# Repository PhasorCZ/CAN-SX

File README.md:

# CAN-SX
Modular automotive electronics system based on CAN bus for resto-mods.

### Description
xxx

### Motivation
xxx

### License
- SOFTWARE: GNU General Public License Version 3
- HARDWARE: CERN Open Hardware Licence Version 2 - Strongly Reciprocal

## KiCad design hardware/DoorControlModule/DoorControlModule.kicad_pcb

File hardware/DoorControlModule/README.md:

# Door Control Module
xxx

### Description
xxx

### License
CERN Open Hardware Licence Version 2 - Strongly Reciprocal

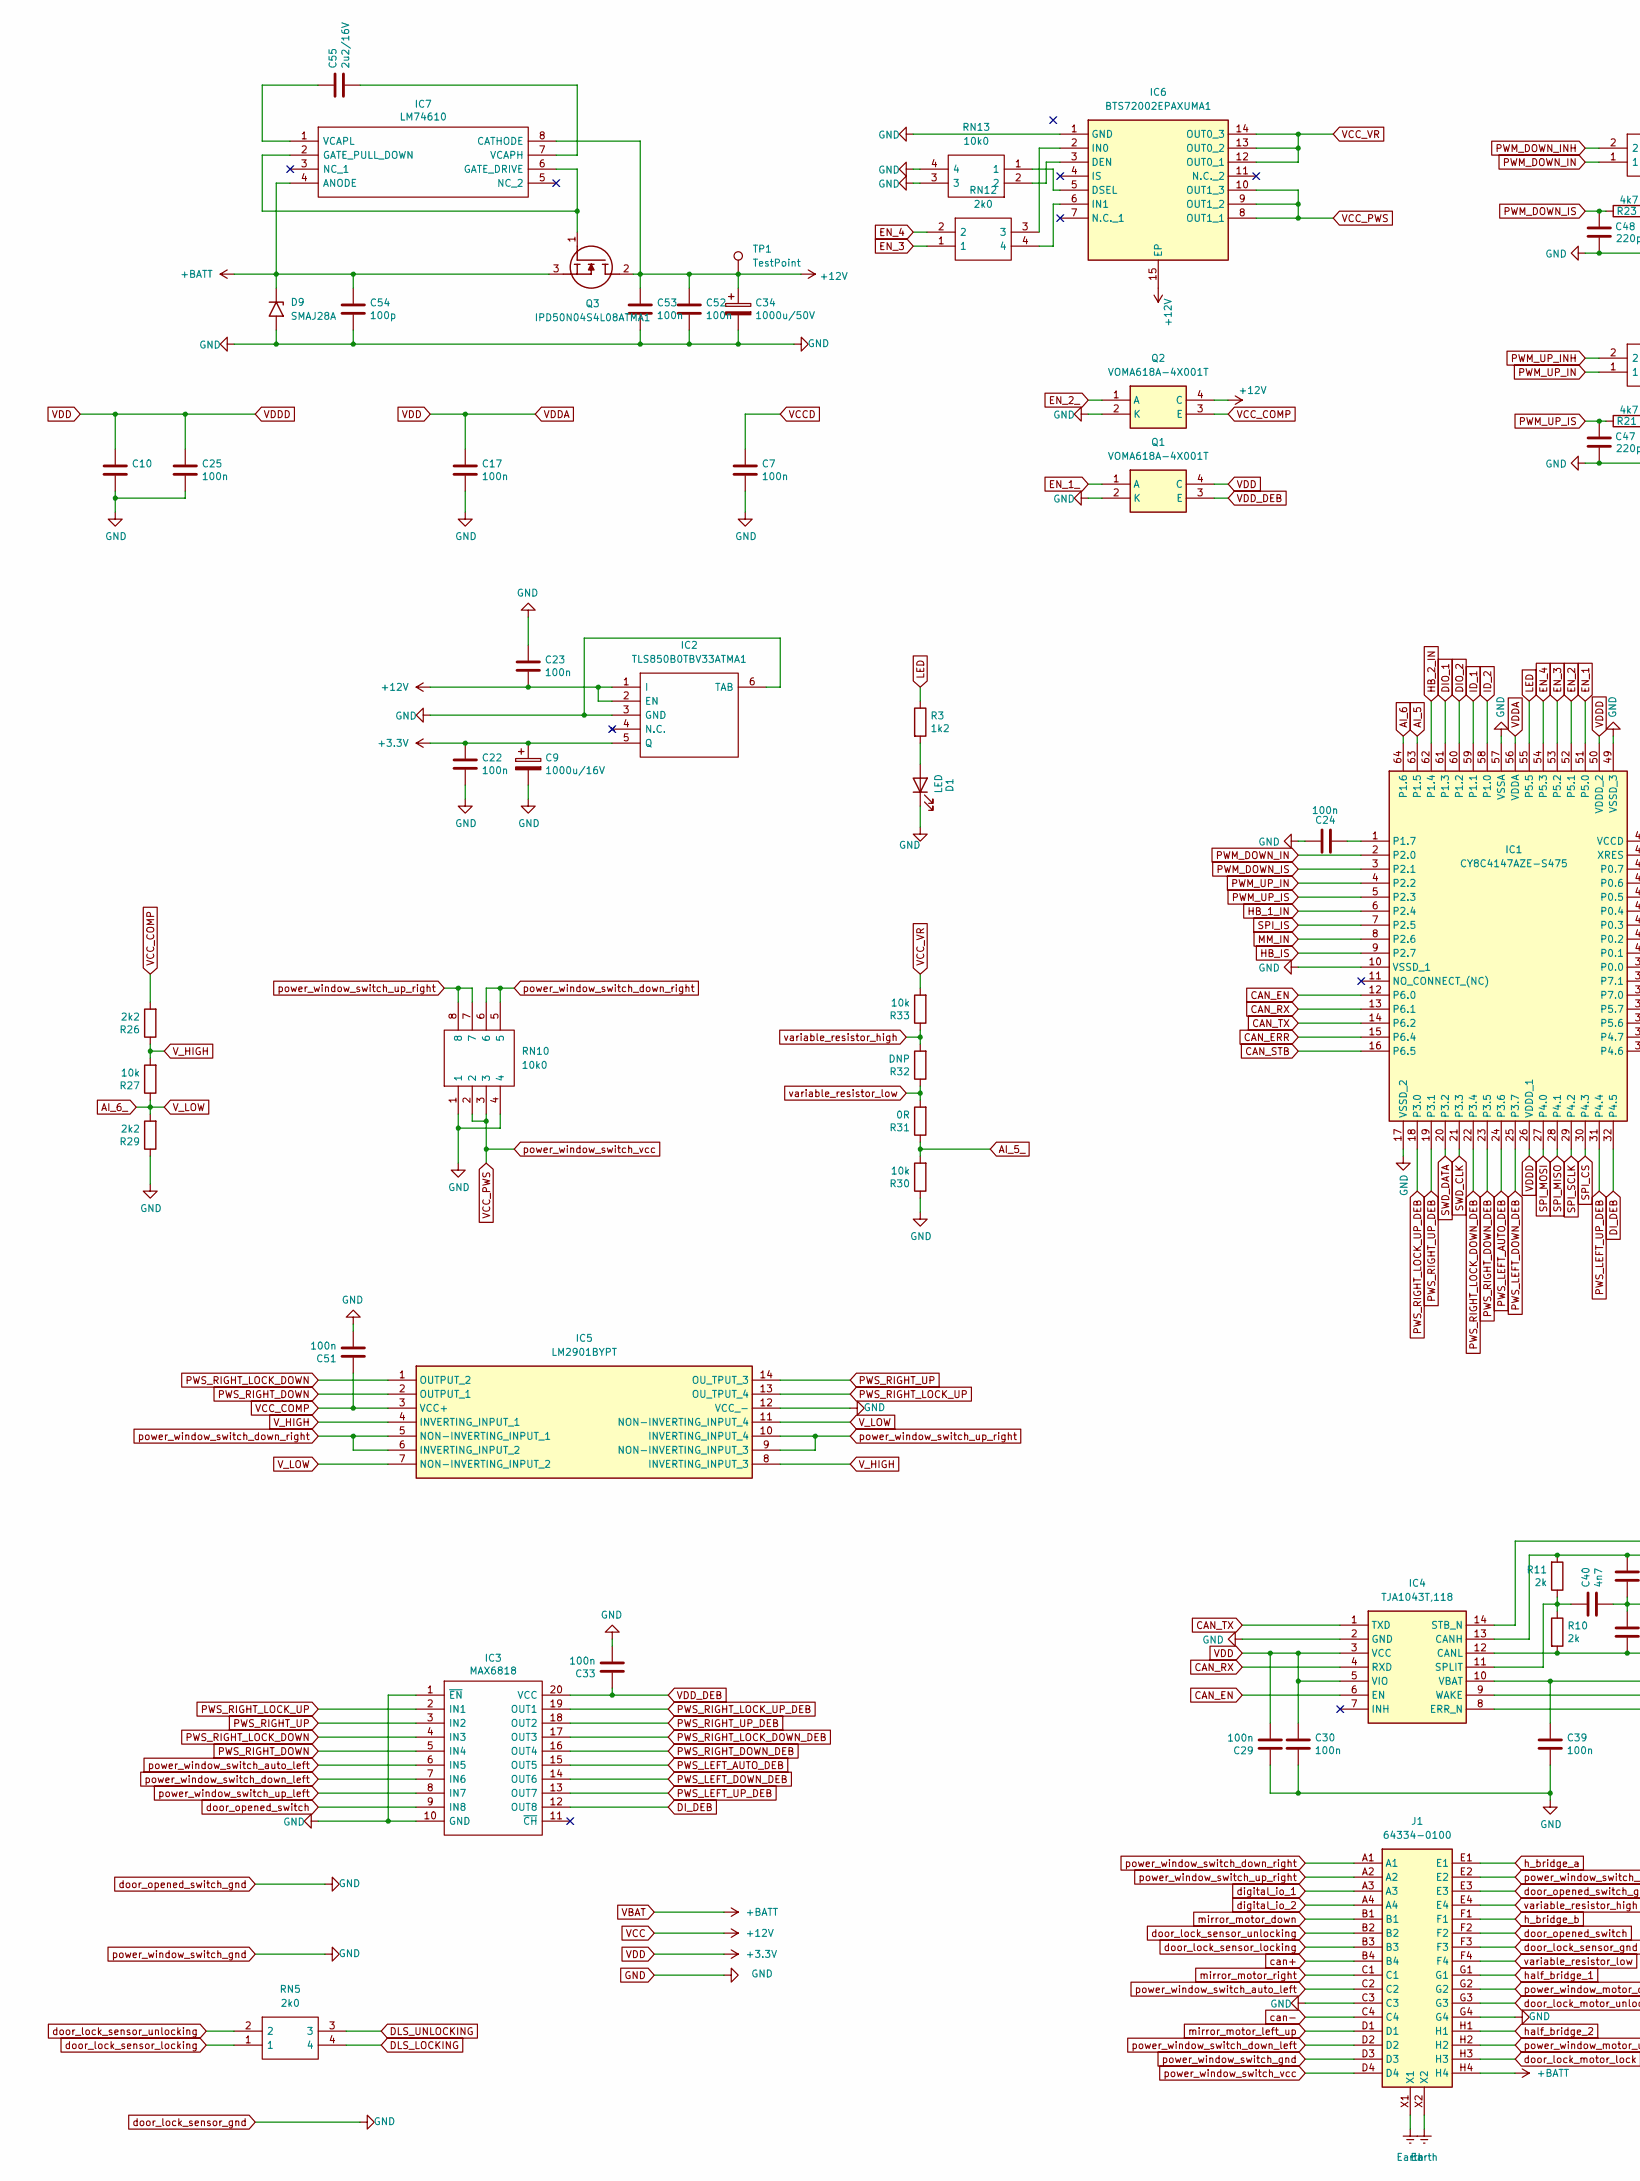
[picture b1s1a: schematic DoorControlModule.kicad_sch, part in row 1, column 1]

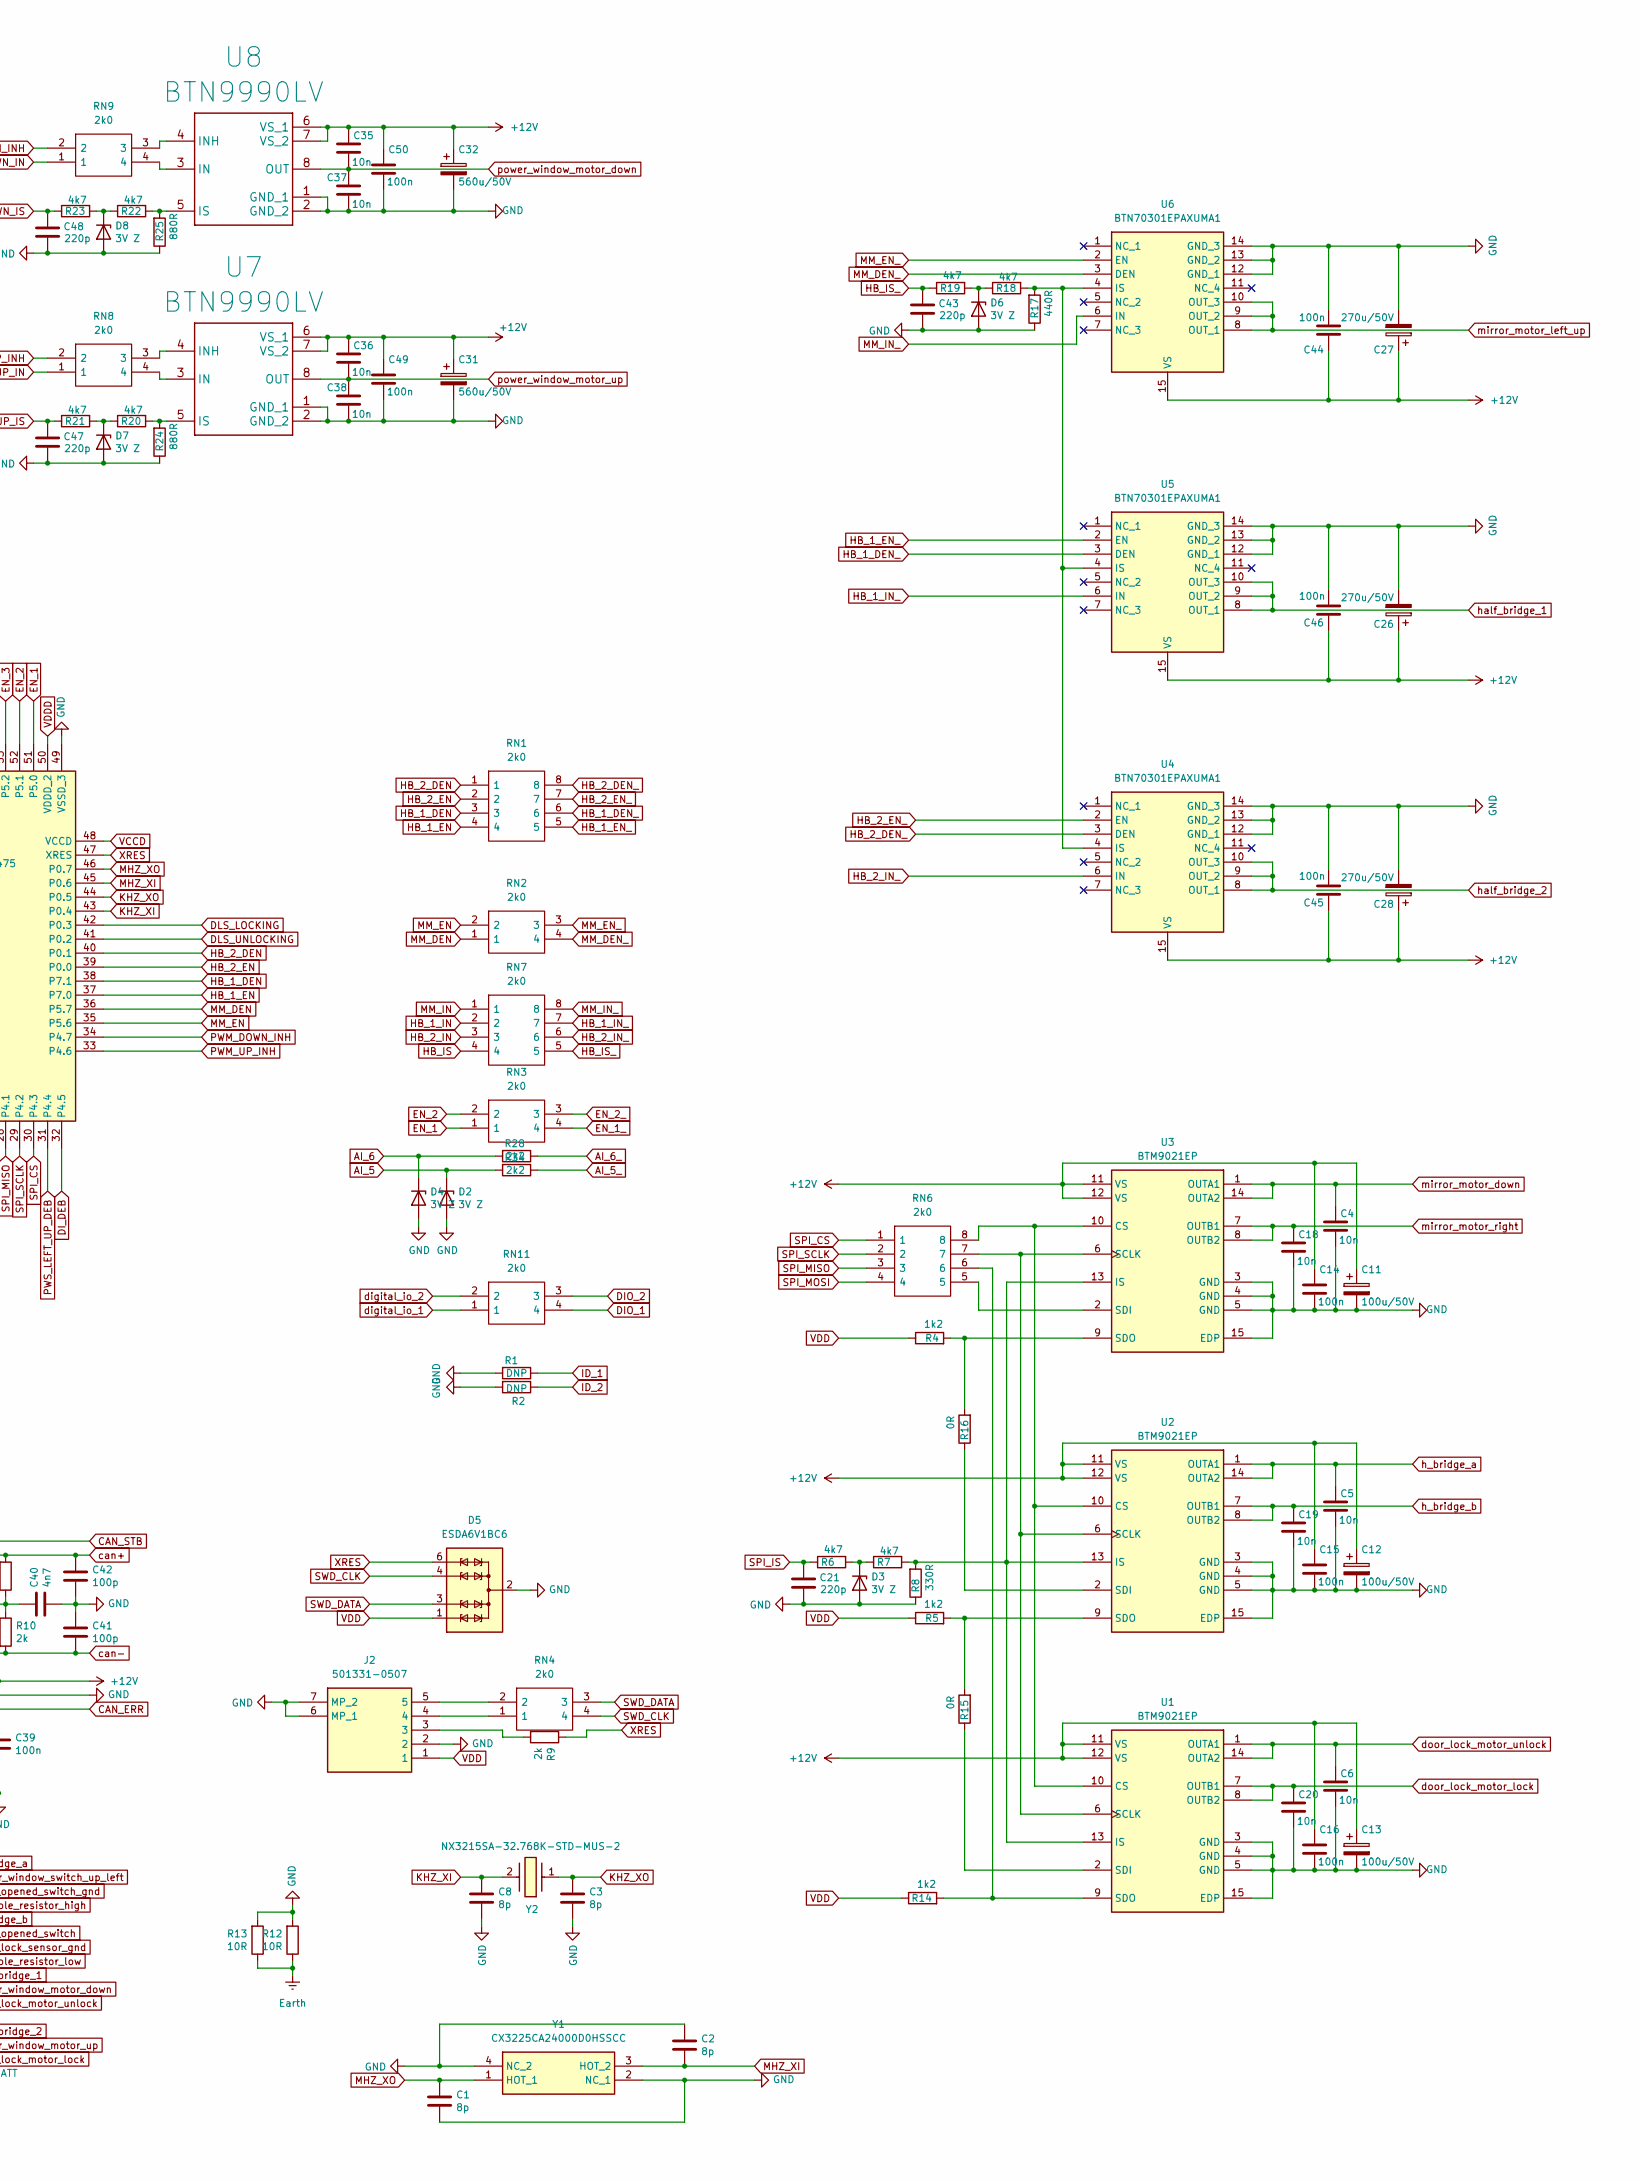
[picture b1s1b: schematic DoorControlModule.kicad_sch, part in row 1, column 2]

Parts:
C1, C2, C3, C8: 8p; C_0603_1608Metric_Pad1.08x0.95mm_HandSolder
C4, C5, C6, C18, C19, C20, C35, C36, C37, C38: 10n; C_0603_1608Metric_Pad1.08x0.95mm_HandSolder
C7, C10, C14, C15, C16, C17, C22, C23, C24, C25, C29, C30, C33, C39, C44, C45, C46, C49, C50, C51: 100n; C_0603_1608Metric_Pad1.08x0.95mm_HandSolder
C9: 1000u/16V; CP_Elec_10x7.9
C11, C12, C13: 100u/50V; CP_Elec_5x4.4
C21, C43, C47, C48: 220p; C_0603_1608Metric_Pad1.08x0.95mm_HandSolder
C26, C27, C28: 270u/50V; CP_Elec_6.3x5.9
C31, C32: 560u/50V; CP_Elec_8x6.9
C34: 1000u/50V; CP_Elec_10x7.9
C40: 4n7; C_0603_1608Metric_Pad1.08x0.95mm_HandSolder
C41, C42, C54: 100p; C_0603_1608Metric_Pad1.08x0.95mm_HandSolder
C52, C53: 100n; C_0805_2012Metric_Pad1.18x1.45mm_HandSolder
C55: 2u2/16V; C_0805_2012Metric_Pad1.18x1.45mm_HandSolder
D1: LED; LED_0805_2012Metric_Pad1.15x1.40mm_HandSolder
D2, D3, D4, D6, D7, D8: 3V Z; D_SOD-323_HandSoldering
D5: ESDA6V1BC6; SOT-23-6
D9: SMAJ28A; D_SMA
IC1: CY8C4147AZE-S475; QFP50P1200X1200X160-64N; Mouser Part Number 727-CY8C4147AZE-S475
IC2: TLS850B0TBV33ATMA1; Mouser Part Number 726-TLS850B0TBV33ATM
IC3: MAX6818; SOP65P778X199-20N; Manufacturer_Part_Number MAX6818EAP+T; Mouser Part Number 700-MAX6818EAPT
IC4: TJA1043T,118; SOIC127P600X175-14N; Mouser Part Number 771-TJA1043T118
IC5: LM2901BYPT; SOP65P640X120-14N; Mouser Part Number 511-LM2901BYPT
IC6: BTS72002EPAXUMA1; SOP65P600X115-15N; Mouser Part Number 726-BTS72002EPAXUMA1
IC7: LM74610; SOP65P490X110-8N; Mouser Part Number 595-LM74610QDGKTQ1
J1: 64334-0100; 64334_JO32_2; Mouser Part Number 538-64334-0100
J2: 501331-0507; 5013310507; Mouser Part Number 538-501331-0507
Q1, Q2: VOMA618A-4X001T; SOP254P695X242-4N; Mouser Part Number 78-VOMA618A-4X001T
Q3: IPD50N04S4L08ATMA1; Mouser Part Number 726-IPD50N04S4L08ATM
R1, R2: DNP; R_0603_1608Metric_Pad0.98x0.95mm_HandSolder
R3, R4, R5, R14: 1k2; R_0603_1608Metric_Pad0.98x0.95mm_HandSolder
R6, R7, R18, R19, R20, R21, R22, R23: 4k7; R_0603_1608Metric_Pad0.98x0.95mm_HandSolder
R8: 330R; R_0603_1608Metric_Pad0.98x0.95mm_HandSolder
R9, R10, R11: 2k; R_0603_1608Metric_Pad0.98x0.95mm_HandSolder
R12, R13: 10R; R_0603_1608Metric_Pad0.98x0.95mm_HandSolder
R15, R16: 0R; R_0603_1608Metric_Pad0.98x0.95mm_HandSolder
R17: 440R; R_0603_1608Metric_Pad0.98x0.95mm_HandSolder
R24, R25: 880R; R_0603_1608Metric_Pad0.98x0.95mm_HandSolder
R26, R28, R29, R34: 2k2; R_0603_1608Metric_Pad0.98x0.95mm_HandSolder
R27: 10k; R_0603_1608Metric_Pad0.98x0.95mm_HandSolder
R30, R33: 10k; R_0805_2012Metric_Pad1.20x1.40mm_HandSolder
R31: 0R; R_0805_2012Metric_Pad1.20x1.40mm_HandSolder
R32: DNP; R_0805_2012Metric_Pad1.20x1.40mm_HandSolder
RN1, RN6, RN7: 2k0; CAY1647R0F4LF; Mouser Part Number 652-CAY16-22R0F4LF
RN2, RN3, RN4, RN5, RN8, RN9, RN11, RN12: 2k0; CAY16220J2LF; Mouser Part Number 652-CAY16-220J2LF
RN10: 10k0; CAY1647R0F4LF; Mouser Part Number 652-CAY16-22R0F4LF
RN13: 10k0; CAY16220J2LF; Mouser Part Number 652-CAY16-220J2LF
TP1: TestPoint; TestPoint_Pad_D1.0mm
U1, U2, U3: BTM9021EP; SOP65P600X115-15N-V
U4, U5, U6: BTN70301EPAXUMA1; SOP65P600X115-15N-V; Mouser Part Number 726-BTN70301EPAXUMA1
U7, U8: BTN9990LV; IFX-PG-HSOF-7-1-V
Y1: CX3225CA24000D0HSSCC; Mouser Part Number 581-CX3225CA24DHSSCC
Y2: NX3215SA-32.768K-STD-MUS-2; NX3215SA32768KSTDMUS2; Mouser Part Number 344-NX3215SA32768K2

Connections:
AI_5: D2.1 (K), IC1.63 (P1.5), R34.2
AI_5_: R30.2, R31.1, R34.1
AI_6: D4.1 (K), IC1.64 (P1.6), R28.2
AI_6_: IC5.7 (NON-INVERTING_INPUT_2), IC5.11 (NON-INVERTING_INPUT_4), R27.1, R28.1, R29.2
CAN_EN: IC1.12 (P6.0), IC4.6 (EN)
CAN_ERR: IC1.15 (P6.4), IC4.8 (ERR_N)
CAN_RX: IC1.13 (P6.1), IC4.4 (RXD)
CAN_STB: IC1.16 (P6.5), IC4.14 (STB_N)
CAN_TX: IC1.14 (P6.2), IC4.1 (TXD)
DIO_1: IC1.61 (P1.3), RN11.4
DIO_2: IC1.60 (P1.2), RN11.3
DI_DEB: IC1.32 (P4.5), IC3.12 (OUT8)
DLS_LOCKING: IC1.42 (P0.3), RN5.4
DLS_UNLOCKING: IC1.41 (P0.2), RN5.3
EN_1: IC1.51 (P5.0), RN3.1
EN_1_: Q1.1 (A), RN3.4
EN_2: IC1.52 (P5.1), RN3.2
EN_2_: Q2.1 (A), RN3.3
EN_3: IC1.53 (P5.2), RN12.1
EN_4: IC1.54 (P5.3), RN12.2
Earth: J1.X1, J1.X2, R12.1, R13.1
GND: C1.2, C2.1, C3.2, C4.2, C5.2, C6.2, C7.2, C8.2, C9.2, C10.2, C11.2, C12.2, C13.2, C14.2, C15.2, C16.2, C17.2, C18.2, C19.2, C20.2, C21.2, C22.2, C23.1, C24.1, C25.2, C26.2, C27.2, C28.2, C29.1, C30.2, C31.2, C32.2, C33.2, C34.2, C37.2, C38.2, C39.2, C40.2, C41.1, C42.2, C43.2, C44.2, C45.2, C46.2, C47.2, C48.2, C49.2, C50.2, C51.2, C52.2, C53.2, C54.2, D1.1 (K), D2.2 (A), D3.2 (A), D4.2 (A), D5.2 (COM), D5.5 (COM), D6.2 (A), D7.2 (A), D8.2 (A), D9.2 (A2), IC1.10 (VSSD_1), IC1.17 (VSSD_2), IC1.49 (VSSD_3), IC1.57 (VSSA), IC2.3 (GND), IC2.6 (TAB), IC3.1 (~EN), IC3.10 (GND), IC4.2 (GND), IC4.9 (WAKE), IC5.12 (VCC_-), IC6.1 (GND), J1.C3, J1.D3, J1.E3, J1.F3, J1.G4, J2.2, J2.6 (MP_1), J2.7 (MP_2), Q1.2 (K), Q2.2 (K), R1.2, R2.2, R8.1, R12.2, R13.2, R17.1, R24.1, R25.1, R29.1, R30.1, RN10.1, RN10.4, RN13.3, RN13.4, U1.3 (GND), U1.4 (GND), U1.5 (GND), U1.15 (EDP), U2.3 (GND), U2.4 (GND), U2.5 (GND), U2.15 (EDP), U3.3 (GND), U3.4 (GND), U3.5 (GND), U3.15 (EDP), U4.12 (GND_1), U4.13 (GND_2), U4.14 (GND_3), U5.12 (GND_1), U5.13 (GND_2), U5.14 (GND_3), U6.12 (GND_1), U6.13 (GND_2), U6.14 (GND_3), U7.1 (GND_1), U7.2 (GND_2), U8.1 (GND_1), U8.2 (GND_2), Y1.2 (NC_1), Y1.4 (NC_2)
HB_1_DEN: IC1.38 (P7.1), RN1.3
HB_1_DEN_: RN1.6, U5.3 (DEN)
HB_1_EN: IC1.37 (P7.0), RN1.4
HB_1_EN_: RN1.5, U5.2 (EN)
HB_1_IN: IC1.6 (P2.4), RN7.2
HB_1_IN_: RN7.7, U5.6 (IN)
HB_2_DEN: IC1.40 (P0.1), RN1.1
HB_2_DEN_: RN1.8, U4.3 (DEN)
HB_2_EN: IC1.39 (P0.0), RN1.2
HB_2_EN_: RN1.7, U4.2 (EN)
HB_2_IN: IC1.62 (P1.4), RN7.3
HB_2_IN_: RN7.6, U4.6 (IN)
HB_IS: IC1.9 (P2.7), RN7.4
HB_IS_: C43.1, R19.1, RN7.5
ID_1: IC1.59 (P1.1), R1.1
ID_2: IC1.58 (P1.0), R2.1
KHZ_XI: C8.1, IC1.43 (P0.4), Y2.2
KHZ_XO: C3.1, IC1.44 (P0.5), Y2.1
LED: IC1.55 (P5.5), R3.1
MHZ_XI: C2.2, IC1.45 (P0.6), Y1.3 (HOT_2)
MHZ_XO: C1.1, IC1.46 (P0.7), Y1.1 (HOT_1)
MM_DEN: IC1.36 (P5.7), RN2.1
MM_DEN_: RN2.4, U6.3 (DEN)
MM_EN: IC1.35 (P5.6), RN2.2
MM_EN_: RN2.3, U6.2 (EN)
MM_IN: IC1.8 (P2.6), RN7.1
MM_IN_: RN7.8, U6.6 (IN)
unnamed: D1.2 (A), R3.2
unnamed: D3.1 (K), R6.2, R7.1
unnamed: D6.1 (K), R18.1, R19.2
unnamed: D7.1 (K), R20.1, R21.2
unnamed: D8.1 (K), R22.1, R23.2
unnamed: C24.2, IC1.1 (P1.7)
unnamed: C40.1, IC4.11 (SPLIT), R10.1, R11.1
unnamed: IC6.3 (DEN), RN13.2
unnamed: IC6.5 (DSEL), RN13.1
unnamed: IC6.2 (IN0), RN12.3
unnamed: IC6.6 (IN1), RN12.4
unnamed: IC7.2 (GATE_PULL_DOWN), IC7.6 (GATE_DRIVE), Q3.1 (G)
unnamed: C55.2, IC7.7 (VCAPH)
unnamed: C55.1, IC7.1 (VCAPL)
unnamed: J2.3, R9.2
unnamed: J2.4, RN4.1
unnamed: J2.5, RN4.2
unnamed: RN6.8, U1.10 (CS), U2.10 (CS), U3.10 (CS)
unnamed: R7.2, R8.2, U1.13 (IS), U2.13 (IS), U3.13 (IS)
unnamed: RN6.7, U1.6 (SCLK), U2.6 (SCLK), U3.6 (SCLK)
unnamed: R15.1, U1.2 (SDI)
unnamed: R14.2, RN6.6, U1.9 (SDO)
unnamed: R16.1, U2.2 (SDI)
unnamed: R5.2, R15.2, U2.9 (SDO)
unnamed: RN6.5, U3.2 (SDI)
unnamed: R4.2, R16.2, U3.9 (SDO)
unnamed: R17.2, R18.2, U4.4 (IS), U5.4 (IS), U6.4 (IS)
unnamed: RN8.4, U7.3 (IN)
unnamed: RN8.3, U7.4 (INH)
unnamed: R20.2, R24.2, U7.5 (IS)
unnamed: RN9.4, U8.3 (IN)
unnamed: RN9.3, U8.4 (INH)
unnamed: R22.2, R25.2, U8.5 (IS)
PWM_DOWN_IN: IC1.2 (P2.0), RN9.1
PWM_DOWN_INH: IC1.34 (P4.7), RN9.2
PWM_DOWN_IS: C48.1, IC1.3 (P2.1), R23.1
PWM_UP_IN: IC1.4 (P2.2), RN8.1
PWM_UP_INH: IC1.33 (P4.6), RN8.2
PWM_UP_IS: C47.1, IC1.5 (P2.3), R21.1
PWS_LEFT_AUTO_DEB: IC1.24 (P3.6), IC3.15 (OUT5)
PWS_LEFT_DOWN_DEB: IC1.25 (P3.7), IC3.14 (OUT6)
PWS_LEFT_UP_DEB: IC1.31 (P4.4), IC3.13 (OUT7)
PWS_RIGHT_DOWN: IC3.5 (IN4), IC5.2 (OUTPUT_1)
PWS_RIGHT_DOWN_DEB: IC1.23 (P3.5), IC3.16 (OUT4)
PWS_RIGHT_LOCK_DOWN: IC3.4 (IN3), IC5.1 (OUTPUT_2)
PWS_RIGHT_LOCK_DOWN_DEB: IC1.22 (P3.4), IC3.17 (OUT3)
PWS_RIGHT_LOCK_UP: IC3.2 (IN1), IC5.13 (OU_TPUT_4)
PWS_RIGHT_LOCK_UP_DEB: IC1.18 (P3.0), IC3.19 (OUT1)
PWS_RIGHT_UP: IC3.3 (IN2), IC5.14 (OU_TPUT_3)
PWS_RIGHT_UP_DEB: IC1.19 (P3.1), IC3.18 (OUT2)
SPI_CS: IC1.30 (P4.3), RN6.1
SPI_IS: C21.1, IC1.7 (P2.5), R6.1
SPI_MISO: IC1.28 (P4.1), RN6.3
SPI_MOSI: IC1.27 (P4.0), RN6.4
SPI_SCLK: IC1.29 (P4.2), RN6.2
SWD_CLK: D5.4 (TVS3), IC1.21 (P3.3), RN4.4
SWD_DATA: D5.3 (TVS2), IC1.20 (P3.2), RN4.3
VBAT: C54.1, D9.1 (A1), IC7.4 (ANODE), J1.H4, Q3.3 (S)
VCC: C11.1, C12.1, C13.1, C14.1, C15.1, C16.1, C23.2, C26.1, C27.1, C28.1, C31.1, C32.1, C34.1, C35.1, C36.1, C39.1, C44.1, C45.1, C46.1, C49.1, C50.1, C52.1, C53.1, IC2.1 (I), IC2.2 (EN), IC4.10 (VBAT), IC6.15 (EP), IC7.8 (CATHODE), Q2.4 (C), Q3.2 (D), TP1.1 (1_1), U1.11 (VS), U1.12 (VS), U2.11 (VS), U2.12 (VS), U3.11 (VS), U3.12 (VS), U4.15 (VS), U5.15 (VS), U6.15 (VS), U7.6 (VS_1), U7.7 (VS_2), U8.6 (VS_1), U8.7 (VS_2)
VCCD: C7.1, IC1.48 (VCCD)
VCC_COMP: C51.1, IC5.3 (VCC+), Q2.3 (E), R26.2
VCC_PWS: IC6.8 (OUT1_1), IC6.9 (OUT1_2), IC6.10 (OUT1_3), J1.D4, RN10.2, RN10.3
VCC_VR: IC6.12 (OUT0_1), IC6.13 (OUT0_2), IC6.14 (OUT0_3), R33.2
VDD: C9.1, C10.1, C17.1, C22.1, C25.1, C29.2, C30.1, D5.1 (TVS1), IC1.26 (VDDD_1), IC1.50 (VDDD_2), IC1.56 (VDDA), IC2.5 (Q), IC4.3 (VCC), IC4.5 (VIO), J2.1, Q1.4 (C), R4.1, R5.1, R14.1
VDD_DEB: C33.1, IC3.20 (VCC), Q1.3 (E)
V_HIGH: IC5.4 (INVERTING_INPUT_1), IC5.8 (INVERTING_INPUT_3), R26.1, R27.2
XRES: D5.6 (TVS4), IC1.47 (XRES), R9.1
can+: C42.1, IC4.13 (CANH), J1.B4, R11.2
can-: C41.2, IC4.12 (CANL), J1.C4, R10.2
digital_io_1: J1.A3, RN11.1
digital_io_2: J1.A4, RN11.2
door_lock_motor_lock: C20.1, J1.H3, U1.7 (OUTB1), U1.8 (OUTB2)
door_lock_motor_unlock: C6.1, J1.G3, U1.1 (OUTA1), U1.14 (OUTA2)
door_lock_sensor_locking: J1.B3, RN5.1
door_lock_sensor_unlocking: J1.B2, RN5.2
door_opened_switch: IC3.9 (IN8), J1.F2
h_bridge_a: C5.1, J1.E1, U2.1 (OUTA1), U2.14 (OUTA2)
h_bridge_b: C19.1, J1.F1, U2.7 (OUTB1), U2.8 (OUTB2)
half_bridge_1: J1.G1, U5.8 (OUT_1), U5.9 (OUT_2), U5.10 (OUT_3)
half_bridge_2: J1.H1, U4.8 (OUT_1), U4.9 (OUT_2), U4.10 (OUT_3)
mirror_motor_down: C4.1, J1.B1, U3.1 (OUTA1), U3.14 (OUTA2)
mirror_motor_left_up: J1.D1, U6.8 (OUT_1), U6.9 (OUT_2), U6.10 (OUT_3)
mirror_motor_right: C18.1, J1.C1, U3.7 (OUTB1), U3.8 (OUTB2)
power_window_motor_down: C35.2, C37.1, J1.G2, U8.8 (OUT)
power_window_motor_up: C36.2, C38.1, J1.H2, U7.8 (OUT)
power_window_switch_auto_left: IC3.6 (IN5), J1.C2
power_window_switch_down_left: IC3.7 (IN6), J1.D2
power_window_switch_down_right: IC5.5 (NON-INVERTING_INPUT_1), IC5.6 (INVERTING_INPUT_2), J1.A1, RN10.5, RN10.6
power_window_switch_up_left: IC3.8 (IN7), J1.E2
power_window_switch_up_right: IC5.9 (NON-INVERTING_INPUT_3), IC5.10 (INVERTING_INPUT_4), J1.A2, RN10.7, RN10.8
variable_resistor_high: J1.E4, R32.2, R33.1
variable_resistor_low: J1.F4, R31.2, R32.1

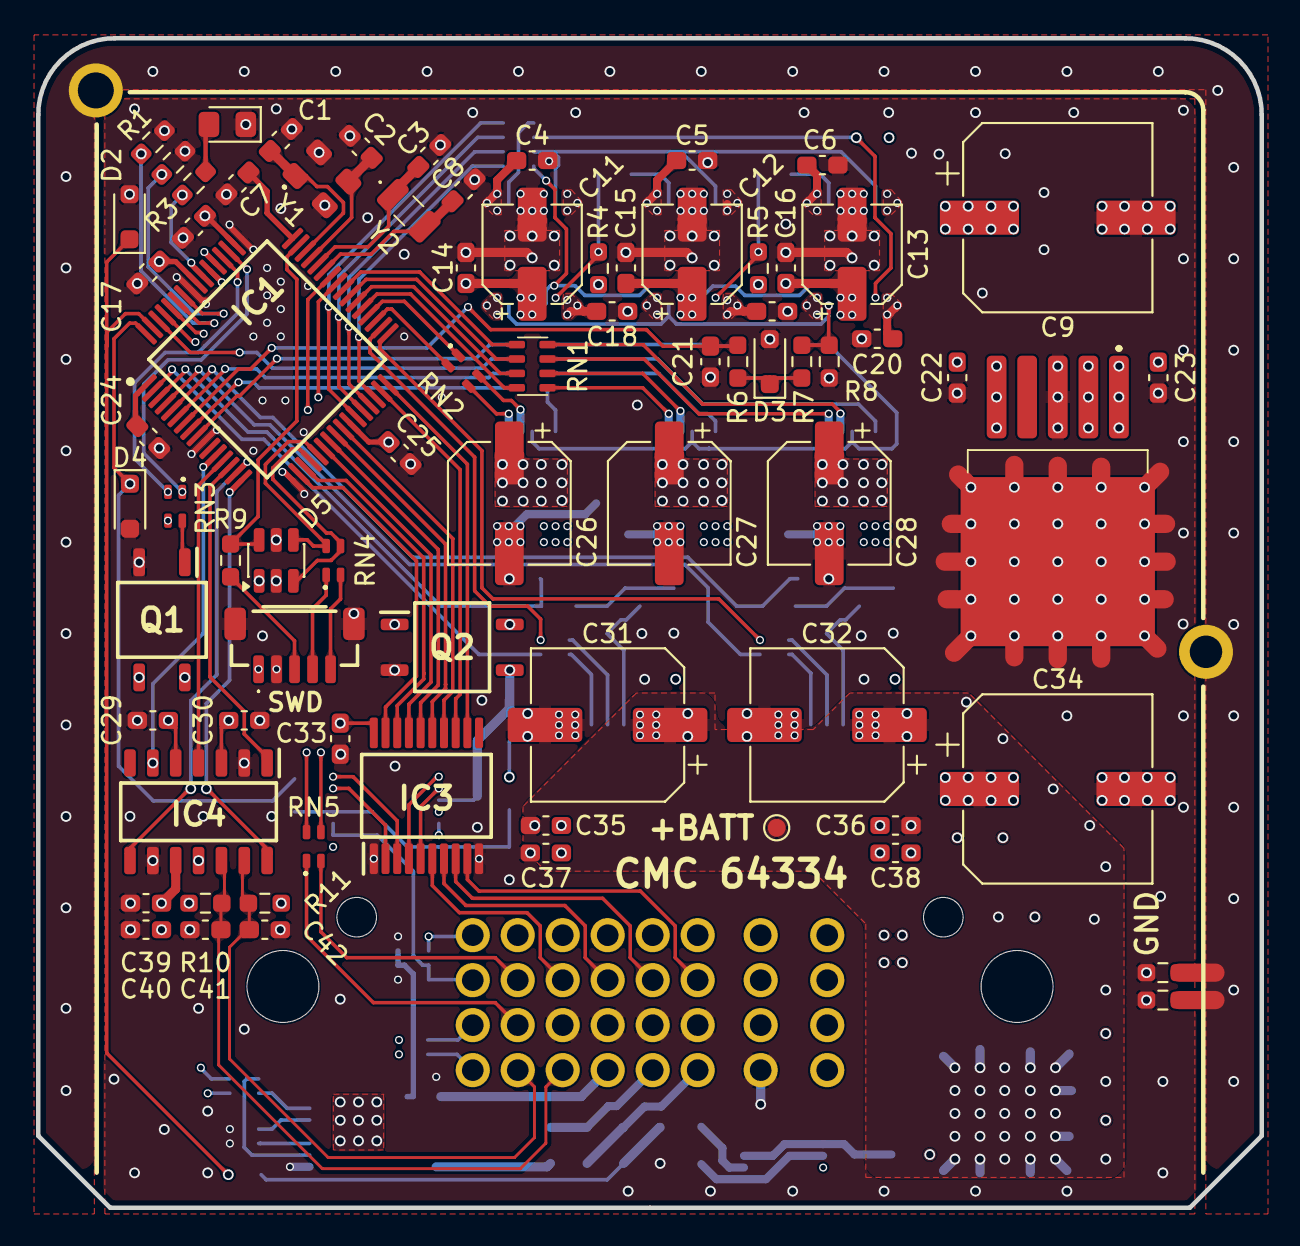
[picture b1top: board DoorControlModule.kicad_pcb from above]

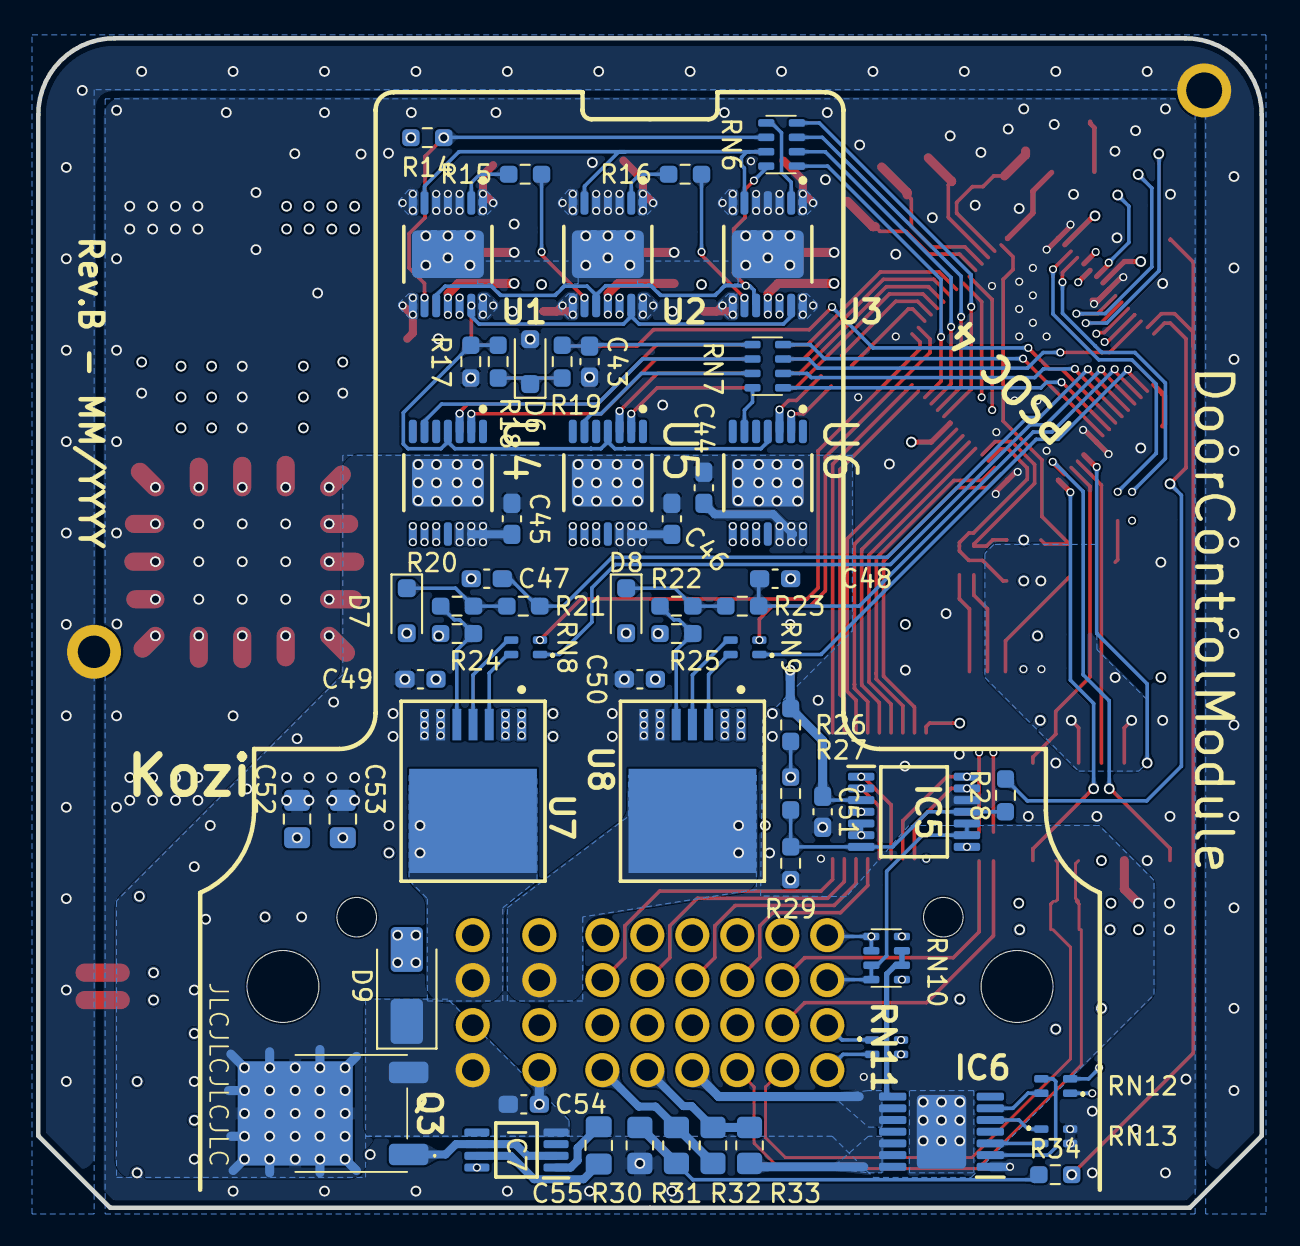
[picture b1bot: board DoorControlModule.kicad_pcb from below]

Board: 6 copper layers, 68.0 x 65.0 mm, 134 parts (58 on the bottom side), 141 nets.

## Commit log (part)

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2026-03-08 initial commit for .gitignore, KiCAD template
    https://github.com/github/gitignore/blob/main/KiCad.gitignore
2026-03-08 license update
    SW - GNU GENERAL PUBLIC LICENSE Version 3
    HW - CERN Open Hardware Licence Version 2 - Strongly Reciprocal
2026-03-08 initial commit for DoorControlModule - Rev.A
2026-03-08 README update
    structure draft, license update
2026-03-08 DoorControlModule Rev.A - production files added
2026-03-08 README files added to sub-folders
2026-03-20 PSoC projects initial commit
2026-04-28 KiCAD .history added to .gitignore
2026-04-28 comparator routing updated
2026-05-04 bootloader_can implemented
